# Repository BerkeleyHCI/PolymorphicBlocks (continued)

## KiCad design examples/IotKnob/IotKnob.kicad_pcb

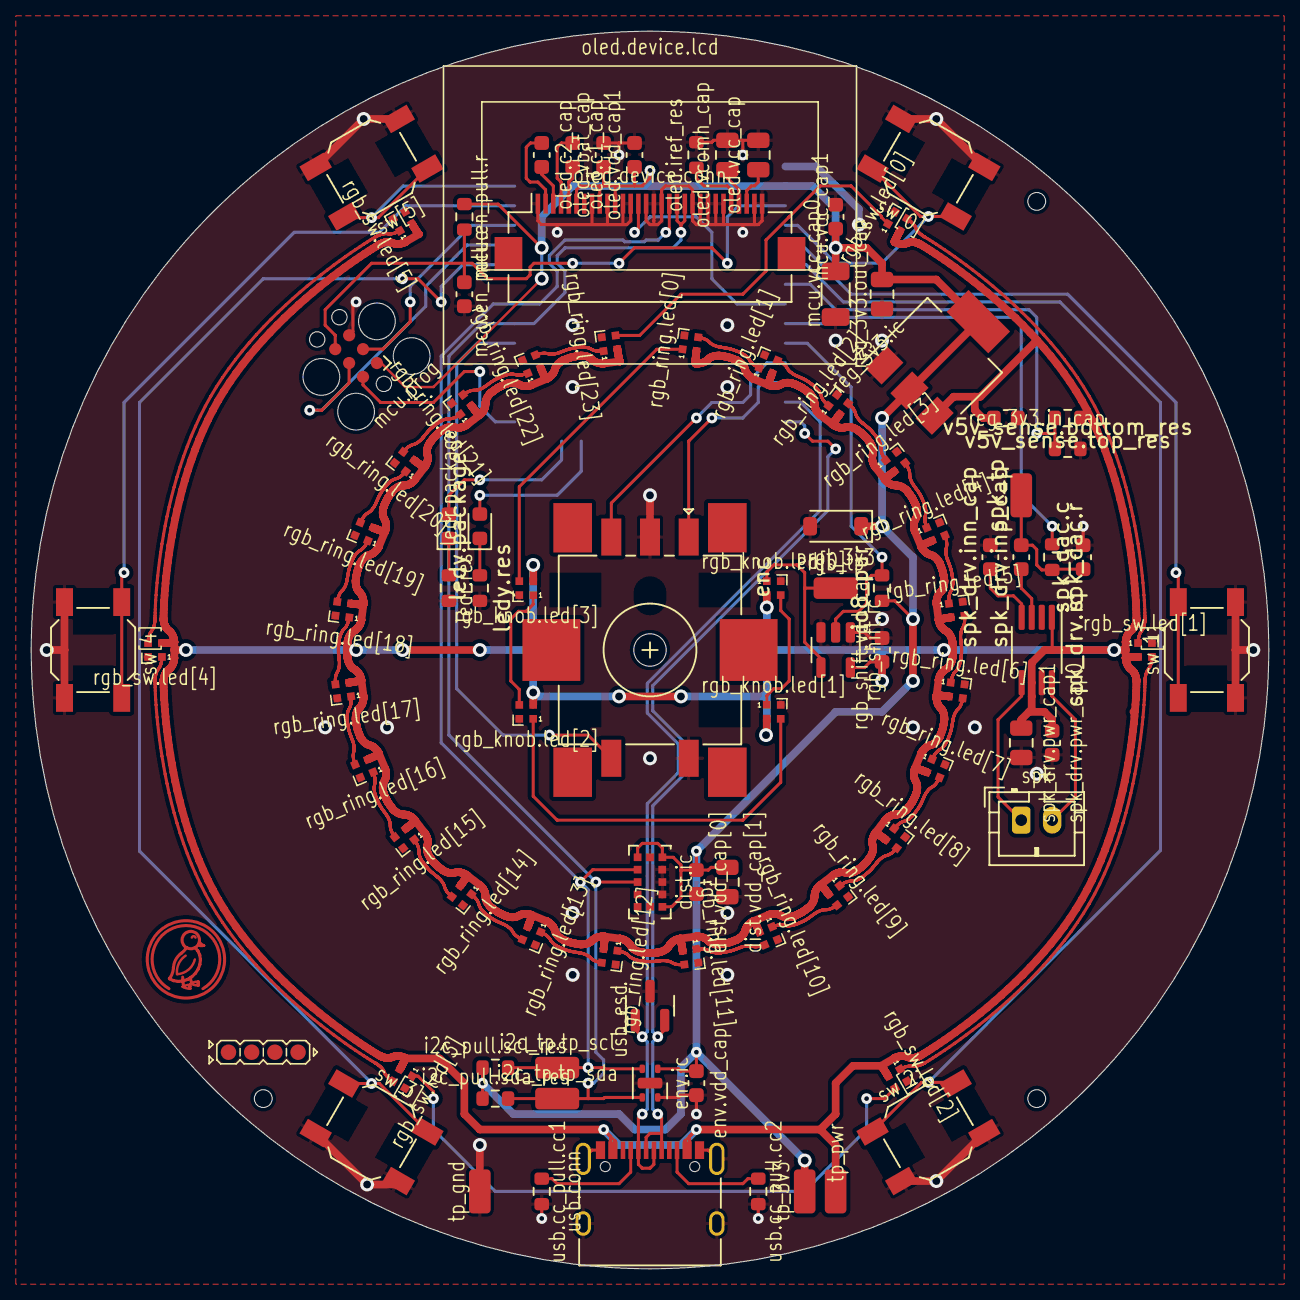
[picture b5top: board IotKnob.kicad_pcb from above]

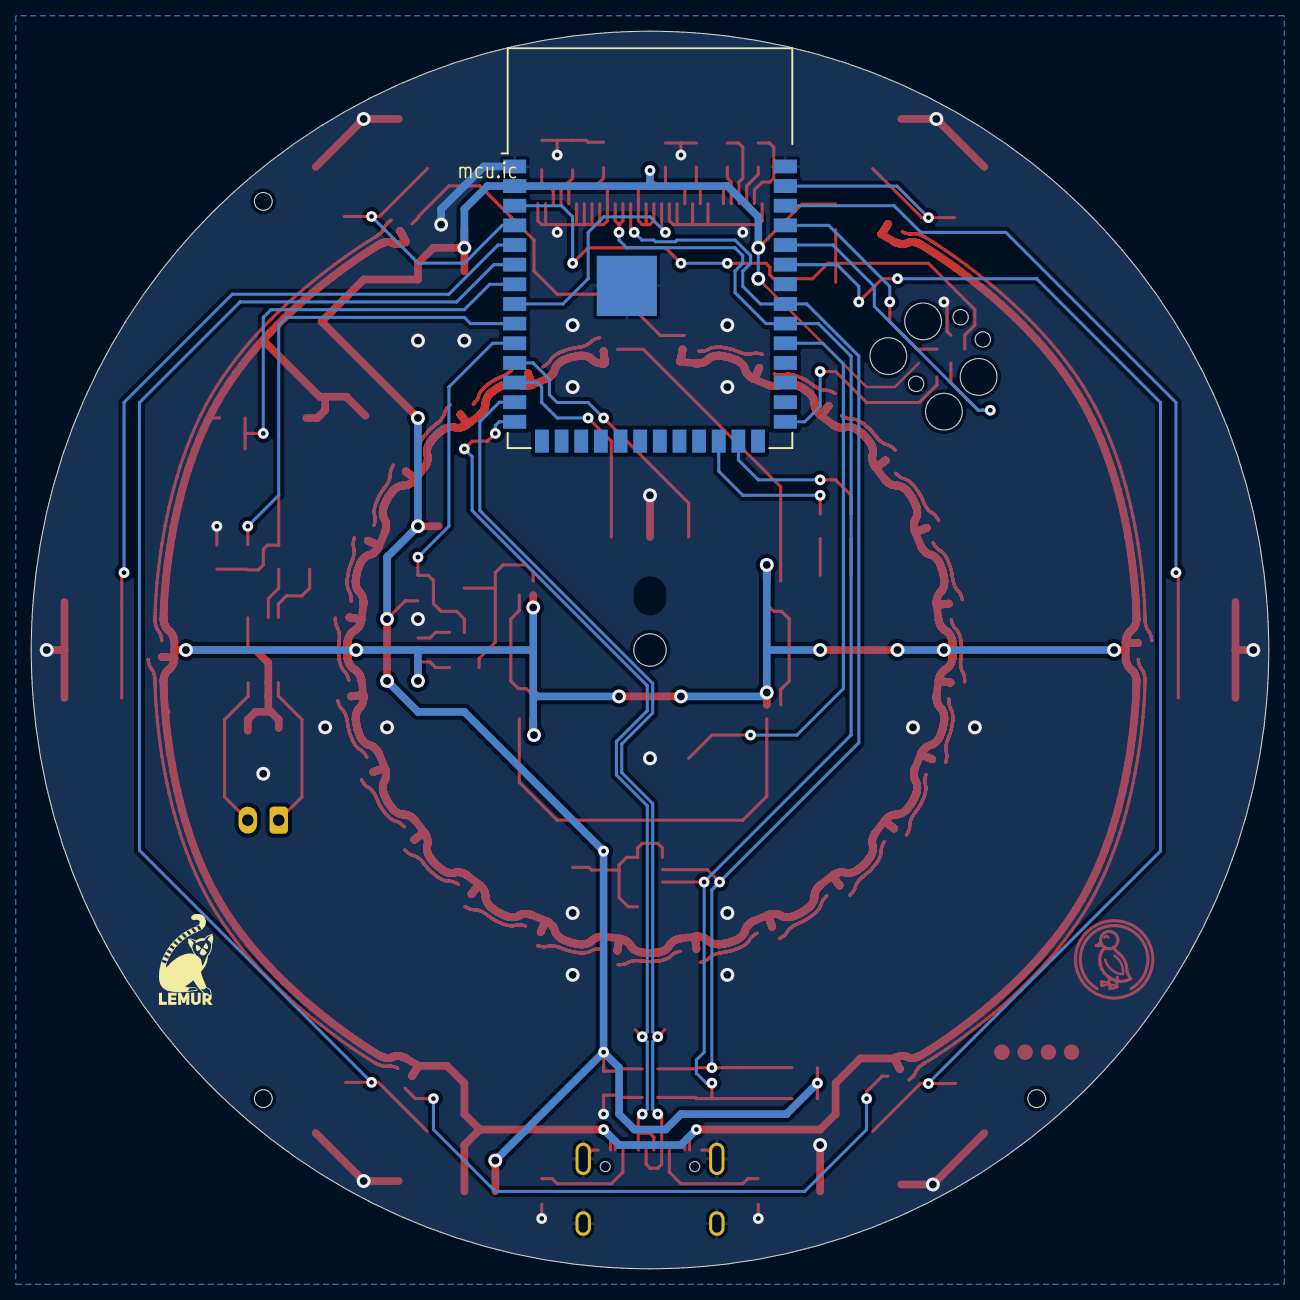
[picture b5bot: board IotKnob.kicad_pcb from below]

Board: 2 copper layers, 80.0 x 80.0 mm, 101 parts (2 on the bottom side), 76 nets.

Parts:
UU4: Duck; Symbol_Duckling
UU5: Lemur; Symbol_LemurSmall
UU6: IdDots4; Indicator_IdDots_4
dist.ic: VL53L0X (STMicroelectronics); ST_VL53L0X
dist.vdd_cap[0]: C_0603_1608Metric
dist.vdd_cap[1]: C_0805_2012Metric
enc: EC11J1525402 (Alps Alpine); RotaryEncoder_Alps_EC11J15-Switch
env.ic: SHTC3 (Sensirion AG); Sensirion_DFN-4-1EP_2x2mm_P1mm_EP0.7x1.6mm
env.vdd_cap: C_0603_1608Metric
i2c_pull.scl_res, i2c_pull.sda_res: R_0603_1608Metric
i2c_tp.tp_scl: 5015 (Keystone) - i2c_chain_0.scl; TestPoint_TE_RCT_0805
i2c_tp.tp_sda: 5015 (Keystone) - i2c_tp._io_sda_link; TestPoint_TE_RCT_0805
io8_pur: R_0603_1608Metric
jlc_th.th1, jlc_th.th2, jlc_th.th3: JlcToolingHole_1.152mm
ledr.package: KT-0603R (Hubei KENTO Elec) - Red 615~630nm 1.9~2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; LED_0603_1608Metric
ledr.res: R_0603_1608Metric
ledy.package: LED_0603_1608Metric
ledy.res: R_0603_1608Metric
mcu.en_pull.c, mcu.vcc_cap1: C_0603_1608Metric
mcu.en_pull.r: R_0603_1608Metric
mcu.ic: ESP32-S3-WROOM-1-N16R8 (Espressif Systems); ESP32-S3-WROOM-1
mcu.prog: Tag-Connect_TC2030-IDC-FP_2x03_P1.27mm_Vertical
mcu.vcc_cap0: C_1206_3216Metric
oled.c1_cap, oled.c2_cap, oled.vbat_cap, oled.vdd_cap1: C_0603_1608Metric
oled.device.conn: AFC01-S30FCA-00 (Jushuo); Hirose_FH12-30S-0.5SH_1x30-1MP_P0.50mm_Horizontal
oled.device.lcd: ER-OLED-0.96-1.1 (EastRising); Lcd_Er_Oled0.96_1.1_Outline
oled.iref_res: R_0603_1608Metric
oled.vcc_cap, oled.vcomh_cap: C_0805_2012Metric
prot_3v3: BZT52C3V6 (SMC(Sangdest Microelectronicstronic (N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; D_SOD-123
reg_3v3.ic: LDL1117S33R (STMicroelectronics); SOT-223-3_TabPin2
reg_3v3.in_cap: C_0603_1608Metric
reg_3v3.out_cap: C_0805_2012Metric
rgb_knob.led[0], rgb_knob.led[1], rgb_knob.led[2], rgb_knob.led[3]: SK6805-EC15 (Opsco Optoelectronics); LED_SK6812_EC15_1.5x1.5mm
rgb_ring.led[0], rgb_ring.led[1], rgb_ring.led[2], rgb_ring.led[3], rgb_ring.led[4], rgb_ring.led[5], rgb_ring.led[6], rgb_ring.led[7], rgb_ring.led[8], rgb_ring.led[9], rgb_ring.led[10], rgb_ring.led[11], rgb_ring.led[12], rgb_ring.led[13], rgb_ring.led[14], rgb_ring.led[15], rgb_ring.led[16], rgb_ring.led[17], rgb_ring.led[18], rgb_ring.led[19], rgb_ring.led[20], rgb_ring.led[21], rgb_ring.led[22], rgb_ring.led[23]: SK6805-EC15 (Opsco Optoelectronics); LED_SK6812_EC15_1.5x1.5mm
rgb_shift.ic: 74AHCT1G125W5-7 (Diodes Incorporated); SOT-23-5
rgb_shift.vdd_cap: C_0603_1608Metric
rgb_sw.led[0], rgb_sw.led[1], rgb_sw.led[2], rgb_sw.led[3], rgb_sw.led[4], rgb_sw.led[5]: SK6805-EC15 (Opsco Optoelectronics); LED_SK6812_EC15_1.5x1.5mm
rgb_tp: 5015 (Keystone) - _rgb_shift_output_link; TestPoint_TE_RCT_0805
spk: B2B-PH-K (JST); JST_PH_B2B-PH-K_1x02_P2.00mm_Vertical
spk_dac.c: C_0603_1608Metric
spk_dac.r: R_0603_1608Metric
spk_drv.ic: PAM8302AASCR (Diodes Incorporated); MSOP-8_3x3mm_P0.65mm
spk_drv.inn_cap, spk_drv.inp_cap, spk_drv.pwr_cap0: C_0603_1608Metric
spk_drv.pwr_cap1: C_0805_2012Metric
spk_tp: 5015 (Keystone) - _spk_dac_output_link; TestPoint_TE_RCT_0805
sw[0], sw[1], sw[2], sw[3], sw[4], sw[5]: 5.1mm switch; SW_SPST_SKQG_WithoutStem
tp_3v3: 5015 (Keystone) - v3v3; TestPoint_TE_RCT_0805
tp_gnd: 5015 (Keystone) - gnd; TestPoint_TE_RCT_0805
tp_pwr: 5015 (Keystone) - vusb; TestPoint_TE_RCT_0805
usb.cc_pull.cc1, usb.cc_pull.cc2: R_0603_1608Metric
usb.conn: COM-15111 (Sparkfun); USB_C_Receptacle_XKB_U262-16XN-4BVC11
usb_esd: PESD5V0X1BT (Nexperia); SOT-23
v5v_sense.bottom_res, v5v_sense.top_res: R_0603_1608Metric

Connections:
enc.a: enc.A, mcu.ic.12
enc.b: enc.B, mcu.ic.11
enc.sw: enc.S1, mcu.ic.31
gnd: dist.ic.2, dist.ic.3, dist.ic.4, dist.ic.6, dist.ic.12, dist.vdd_cap[0].2, dist.vdd_cap[1].2, enc.C, enc.S2, env.ic.4, env.ic.5, env.vdd_cap.2, ledr.res.2, ledy.res.2, mcu.en_pull.c.2, mcu.ic.1, mcu.ic.40, mcu.ic.41, mcu.prog.5, mcu.vcc_cap0.2, mcu.vcc_cap1.2, oled.device.conn.1, oled.device.conn.8, oled.device.conn.10, oled.device.conn.12, oled.device.conn.13, oled.device.conn.15, oled.device.conn.16, oled.device.conn.17, oled.device.conn.21, oled.device.conn.22, oled.device.conn.23, oled.device.conn.24, oled.device.conn.25, oled.device.conn.29, oled.device.conn.30, oled.iref_res.2, oled.vbat_cap.2, oled.vcc_cap.2, oled.vcomh_cap.2, oled.vdd_cap1.2, prot_3v3.2, reg_3v3.ic.1, reg_3v3.in_cap.2, reg_3v3.out_cap.2, rgb_knob.led[0].4, rgb_knob.led[1].4, rgb_knob.led[2].4, rgb_knob.led[3].4, rgb_ring.led[0].4, rgb_ring.led[1].4, rgb_ring.led[2].4, rgb_ring.led[3].4, rgb_ring.led[4].4, rgb_ring.led[5].4, rgb_ring.led[6].4, rgb_ring.led[7].4, rgb_ring.led[8].4, rgb_ring.led[9].4, rgb_ring.led[10].4, rgb_ring.led[11].4, rgb_ring.led[12].4, rgb_ring.led[13].4, rgb_ring.led[14].4, rgb_ring.led[15].4, rgb_ring.led[16].4, rgb_ring.led[17].4, rgb_ring.led[18].4, rgb_ring.led[19].4, rgb_ring.led[20].4, rgb_ring.led[21].4, rgb_ring.led[22].4, rgb_ring.led[23].4, rgb_shift.ic.1, rgb_shift.ic.3, rgb_shift.vdd_cap.2, rgb_sw.led[0].4, rgb_sw.led[1].4, rgb_sw.led[2].4, rgb_sw.led[3].4, rgb_sw.led[4].4, rgb_sw.led[5].4, spk_dac.c.2, spk_drv.ic.7, spk_drv.inn_cap.2, spk_drv.pwr_cap0.2, spk_drv.pwr_cap1.2, sw[0].2, sw[1].2, sw[2].2, sw[3].2, sw[4].2, sw[5].2, tp_gnd.1, usb.cc_pull.cc1.1, usb.cc_pull.cc2.1, usb.conn.A1, usb.conn.A12, usb.conn.B1, usb.conn.B12, usb.conn.S1, usb_esd.3, v5v_sense.bottom_res.2
i2c_chain_0.scl: dist.ic.10, env.ic.2, i2c_pull.scl_res.2, i2c_tp.tp_scl.1, mcu.ic.33, oled.device.conn.18
i2c_chain_0.sda: dist.ic.9, env.ic.3, i2c_pull.sda_res.2, i2c_tp.tp_sda.1, mcu.ic.32, oled.device.conn.19, oled.device.conn.20
io8_pur.io: io8_pur.2, mcu.ic.10, rgb_shift.ic.2
ledr.res.a: ledr.package.1, ledr.res.1
ledr.signal: ledr.package.2, mcu.ic.25
ledy.res.a: ledy.package.1, ledy.res.1
ledy.signal: ledy.package.2, mcu.ic.24
mcu.program_boot_node: mcu.ic.27, mcu.prog.2
mcu.program_en_node: mcu.en_pull.c.1, mcu.en_pull.r.2, mcu.ic.3, mcu.prog.6
mcu.program_uart_node.a_tx: mcu.ic.37, mcu.prog.3
mcu.program_uart_node.b_tx: mcu.ic.36, mcu.prog.4
oled.c1_cap.neg: oled.c1_cap.2, oled.device.conn.5
oled.c1_cap.pos: oled.c1_cap.1, oled.device.conn.4
oled.c2_cap.neg: oled.c2_cap.2, oled.device.conn.3
oled.c2_cap.pos: oled.c2_cap.1, oled.device.conn.2
oled.device.vcc: oled.device.conn.28, oled.vcc_cap.1
oled.device.vcomh: oled.device.conn.27, oled.vcomh_cap.1
oled.iref_res.a: oled.device.conn.26, oled.iref_res.1
oled.reset: mcu.ic.8, oled.device.conn.14
rgb_knob.dout: rgb_knob.led[3].3, rgb_ring.led[0].1
rgb_knob.led[0].dout: rgb_knob.led[0].3, rgb_knob.led[1].1
rgb_knob.led[1].dout: rgb_knob.led[1].3, rgb_knob.led[2].1
rgb_knob.led[2].dout: rgb_knob.led[2].3, rgb_knob.led[3].1
rgb_ring.dout: rgb_ring.led[23].3, rgb_sw.led[0].1
rgb_ring.led[0].dout: rgb_ring.led[0].3, rgb_ring.led[1].1
rgb_ring.led[1].dout: rgb_ring.led[1].3, rgb_ring.led[2].1
rgb_ring.led[2].dout: rgb_ring.led[2].3, rgb_ring.led[3].1
rgb_ring.led[3].dout: rgb_ring.led[3].3, rgb_ring.led[4].1
rgb_ring.led[4].dout: rgb_ring.led[4].3, rgb_ring.led[5].1
rgb_ring.led[5].dout: rgb_ring.led[5].3, rgb_ring.led[6].1
rgb_ring.led[6].dout: rgb_ring.led[6].3, rgb_ring.led[7].1
rgb_ring.led[7].dout: rgb_ring.led[7].3, rgb_ring.led[8].1
rgb_ring.led[8].dout: rgb_ring.led[8].3, rgb_ring.led[9].1
rgb_ring.led[9].dout: rgb_ring.led[9].3, rgb_ring.led[10].1
rgb_ring.led[10].dout: rgb_ring.led[10].3, rgb_ring.led[11].1
rgb_ring.led[11].dout: rgb_ring.led[11].3, rgb_ring.led[12].1
rgb_ring.led[12].dout: rgb_ring.led[12].3, rgb_ring.led[13].1
rgb_ring.led[13].dout: rgb_ring.led[13].3, rgb_ring.led[14].1
rgb_ring.led[14].dout: rgb_ring.led[14].3, rgb_ring.led[15].1
rgb_ring.led[15].dout: rgb_ring.led[15].3, rgb_ring.led[16].1
rgb_ring.led[16].dout: rgb_ring.led[16].3, rgb_ring.led[17].1
rgb_ring.led[17].dout: rgb_ring.led[17].3, rgb_ring.led[18].1
rgb_ring.led[18].dout: rgb_ring.led[18].3, rgb_ring.led[19].1
rgb_ring.led[19].dout: rgb_ring.led[19].3, rgb_ring.led[20].1
rgb_ring.led[20].dout: rgb_ring.led[20].3, rgb_ring.led[21].1
rgb_ring.led[21].dout: rgb_ring.led[21].3, rgb_ring.led[22].1
rgb_ring.led[22].dout: rgb_ring.led[22].3, rgb_ring.led[23].1
rgb_shift.output: rgb_knob.led[0].1, rgb_shift.ic.4, rgb_tp.1
rgb_sw.led[0].dout: rgb_sw.led[0].3, rgb_sw.led[1].1
rgb_sw.led[1].dout: rgb_sw.led[1].3, rgb_sw.led[2].1
rgb_sw.led[2].dout: rgb_sw.led[2].3, rgb_sw.led[3].1
rgb_sw.led[3].dout: rgb_sw.led[3].3, rgb_sw.led[4].1
rgb_sw.led[4].dout: rgb_sw.led[4].3, rgb_sw.led[5].1
spk_dac.input: mcu.ic.9, spk_dac.r.1
spk_dac.output: spk_dac.c.1, spk_dac.r.2, spk_drv.inp_cap.2, spk_tp.1
spk_drv.inn_cap.pos: spk_drv.ic.4, spk_drv.inn_cap.1
spk_drv.inp_cap.pos: spk_drv.ic.3, spk_drv.inp_cap.1
spk_drv.spk.a: spk.1, spk_drv.ic.5
spk_drv.spk.b: spk.2, spk_drv.ic.8
sw[0].out: mcu.ic.4, sw[0].1
sw[1].out: mcu.ic.5, sw[1].1
sw[2].out: mcu.ic.6, sw[2].1
sw[3].out: mcu.ic.35, sw[3].1
sw[4].out: mcu.ic.38, sw[4].1
sw[5].out: mcu.ic.39, sw[5].1
usb.conn.A5: usb.cc_pull.cc1.2, usb.conn.A5
usb.conn.B5: usb.cc_pull.cc2.2, usb.conn.B5
usb_chain_0.d_N: mcu.ic.13, usb.conn.A7, usb.conn.B7, usb_esd.1
usb_chain_0.d_P: mcu.ic.14, usb.conn.A6, usb.conn.B6, usb_esd.2
v3v3: dist.ic.1, dist.ic.5, dist.ic.11, dist.vdd_cap[0].1, dist.vdd_cap[1].1, env.ic.1, env.vdd_cap.1, i2c_pull.scl_res.1, i2c_pull.sda_res.1, io8_pur.1, mcu.en_pull.r.1, mcu.ic.2, mcu.prog.1, mcu.vcc_cap0.1, mcu.vcc_cap1.1, oled.device.conn.6, oled.device.conn.9, oled.device.conn.11, oled.vbat_cap.1, oled.vdd_cap1.1, prot_3v3.1, reg_3v3.ic.2, reg_3v3.out_cap.1, tp_3v3.1
v5v_sense.output: mcu.ic.7, v5v_sense.bottom_res.1, v5v_sense.top_res.2
vusb: reg_3v3.ic.3, reg_3v3.in_cap.1, rgb_knob.led[0].2, rgb_knob.led[1].2, rgb_knob.led[2].2, rgb_knob.led[3].2, rgb_ring.led[0].2, rgb_ring.led[1].2, rgb_ring.led[2].2, rgb_ring.led[3].2, rgb_ring.led[4].2, rgb_ring.led[5].2, rgb_ring.led[6].2, rgb_ring.led[7].2, rgb_ring.led[8].2, rgb_ring.led[9].2, rgb_ring.led[10].2, rgb_ring.led[11].2, rgb_ring.led[12].2, rgb_ring.led[13].2, rgb_ring.led[14].2, rgb_ring.led[15].2, rgb_ring.led[16].2, rgb_ring.led[17].2, rgb_ring.led[18].2, rgb_ring.led[19].2, rgb_ring.led[20].2, rgb_ring.led[21].2, rgb_ring.led[22].2, rgb_ring.led[23].2, rgb_shift.ic.5, rgb_shift.vdd_cap.1, rgb_sw.led[0].2, rgb_sw.led[1].2, rgb_sw.led[2].2, rgb_sw.led[3].2, rgb_sw.led[4].2, rgb_sw.led[5].2, spk_drv.ic.1, spk_drv.ic.6, spk_drv.pwr_cap0.1, spk_drv.pwr_cap1.1, tp_pwr.1, usb.conn.A4, usb.conn.A9, usb.conn.B4, usb.conn.B9, v5v_sense.top_res.1

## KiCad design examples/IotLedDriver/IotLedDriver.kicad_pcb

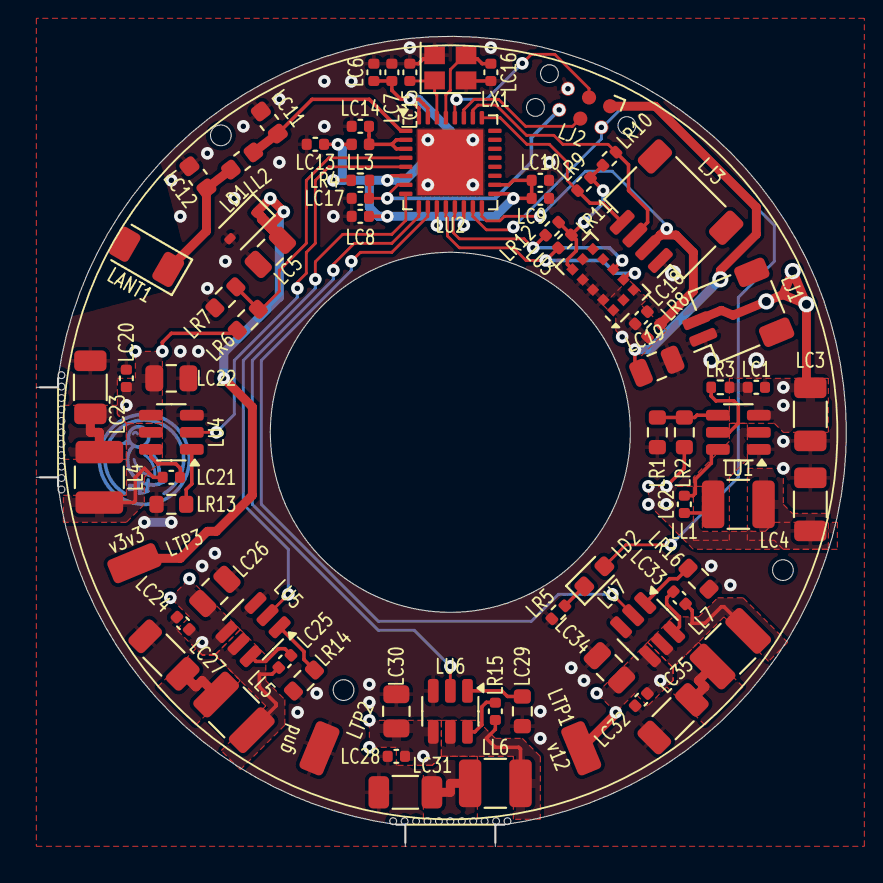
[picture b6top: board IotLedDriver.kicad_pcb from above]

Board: 2 copper layers, 45.0 x 45.0 mm, 79 parts (1 on the bottom side), 43 nets.

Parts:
LANT1: mcu.ant; D_1206_3216Metric
LC1: reg_3v3.hf_in_cap; C_0402_1005Metric
LC2: reg_3v3.boot_cap; C_0402_1005Metric
LC3: reg_3v3.power_path.in_cap; C_1206_3216Metric
LC4: reg_3v3.power_path.out_cap; C_1206_3216Metric
LC5: mcu.vdd_bulk_cap; C_0805_2012Metric
LC6: mcu.vdda_cap0; C_0402_1005Metric
LC7: mcu.vdda_cap1; C_0402_1005Metric
LC8: mcu.vddrtc_cap; C_0402_1005Metric
LC9: mcu.vddcpu_cap; C_0402_1005Metric
LC10: mcu.vddspi_cap; C_0402_1005Metric
LC11: mcu.pi.c1; C_0603_1608Metric
LC12: mcu.pi.c2; C_0603_1608Metric
LC13: mcu.vdd3p3_l_cap; C_0402_1005Metric
LC14: mcu.vdd3p3_cap; C_0402_1005Metric
LC15: mcu.crystal.cap_a; C_0402_1005Metric
LC16: mcu.crystal.cap_b; C_0402_1005Metric
LC17: mcu.en_pull.c; C_0402_1005Metric
LC18: tof.vdd_cap[0]; C_0402_1005Metric
LC19: tof.vdd_cap[1]; C_0805_2012Metric
LC20: led_drv[0].cap; C_0402_1005Metric
LC21: led_drv[0].boot_cap; C_0402_1005Metric
LC22: led_drv[0].power_path.in_cap; C_0805_2012Metric
LC23: led_drv[0].power_path.out_cap; C_1206_3216Metric
LC24: led_drv[1].cap; C_0402_1005Metric
LC25: led_drv[1].boot_cap; C_0402_1005Metric
LC26: led_drv[1].power_path.in_cap; C_0805_2012Metric
LC27: led_drv[1].power_path.out_cap; C_1206_3216Metric
LC28: led_drv[2].cap; C_0402_1005Metric
LC29: led_drv[2].boot_cap; C_0402_1005Metric
LC30: led_drv[2].power_path.in_cap; C_0805_2012Metric
LC31: led_drv[2].power_path.out_cap; C_1206_3216Metric
LC32: led_drv[3].cap; C_0402_1005Metric
LC33: led_drv[3].boot_cap; C_0402_1005Metric
LC34: led_drv[3].power_path.in_cap; C_0805_2012Metric
LC35: led_drv[3].power_path.out_cap; C_1206_3216Metric
LD1: prot_3v3; D_SOD-323
LD2: ledr.package; LED_0603_1608Metric
LH1: jlc_th.th1; JlcToolingHole_1.152mm
LH2: jlc_th.th2; JlcToolingHole_1.152mm
LH3: jlc_th.th3; JlcToolingHole_1.152mm
LJ1: pwr; JST_SH_SM02B-SRSS-TB_1x02-1MP_P1.00mm_Horizontal
LJ2: mcu.prog; Tag-Connect_TC2030-IDC-NL_2x03_P1.27mm_Vertical
LJ3: qwiic; JST_SH_SM04B-SRSS-TB_1x04-1MP_P1.00mm_Horizontal
LL1: reg_3v3.power_path.inductor; L_1210_3225Metric
LL2: mcu.pi.l; L_0603_1608Metric
LL3: mcu.vdd3p3_l; L_0402_1005Metric
LL4: led_drv[0].power_path.inductor; L_1210_3225Metric
LL5: led_drv[1].power_path.inductor; L_1210_3225Metric
LL6: led_drv[2].power_path.inductor; L_1210_3225Metric
LL7: led_drv[3].power_path.inductor; L_1210_3225Metric
LR1: reg_3v3.fb.top_res; R_0603_1608Metric
LR2: reg_3v3.fb.bottom_res; R_0603_1608Metric
LR3: reg_3v3.en_res; R_0402_1005Metric
LR4: mcu.en_pull.r; R_0402_1005Metric
LR5: ledr.res; R_0402_1005Metric
LR6: v12_sense.top_res; R_0603_1608Metric
LR7: v12_sense.bottom_res; R_0603_1608Metric
LR8: qwiic_pwr_res; R_0402_1005Metric
LR9: qwiic_pull.scl_res; R_0402_1005Metric
LR10: qwiic_pull.sda_res; R_0402_1005Metric
LR11: tof_pull.scl_res; R_0402_1005Metric
LR12: tof_pull.sda_res; R_0402_1005Metric
LR13: led_drv[0].rsense; R_0603_1608Metric
LR14: led_drv[1].rsense; R_0603_1608Metric
LR15: led_drv[2].rsense; R_0603_1608Metric
LR16: led_drv[3].rsense; R_0603_1608Metric
LTP1: v12; TestPoint_TE_RCT_0805
LTP2: gnd; TestPoint_TE_RCT_0805
LTP3: v3v3; TestPoint_TE_RCT_0805
LU1: reg_3v3.ic; SOT-23-6
LU2: mcu.ic; QFN-32-1EP_5x5mm_P0.5mm_EP3.65x3.65mm
LU3: tof.ic; ST_VL53L0X
LU4: led_drv[0].ic; SOT-23-6
LU5: led_drv[1].ic; SOT-23-6
LU6: led_drv[2].ic; SOT-23-6
LU7: led_drv[3].ic; SOT-23-6
LX1: mcu.crystal.package; Crystal_SMD_2520-4Pin_2.5x2.0mm
UU4: Duck; Symbol_Duckling

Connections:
Lgnd: LC1.2, LC3.2, LC4.2, LC5.2, LC6.2, LC7.2, LC8.2, LC9.2, LC10.2, LC11.2, LC12.2, LC13.2, LC14.2, LC15.2, LC16.2, LC17.2, LC18.2, LC19.2, LC20.2, LC22.2, LC23.2, LC24.2, LC26.2, LC27.2, LC28.2, LC30.2, LC31.2, LC32.2, LC34.2, LC35.2, LD1.2, LJ1.1, LJ2.5, LJ3.1, LR2.2, LR5.2, LR7.2, LR13.1, LR14.1, LR15.1, LR16.1, LTP2.1, LU1.1, LU2.33, LU3.2, LU3.3, LU3.4, LU3.6, LU3.12, LU4.3, LU5.3, LU6.3, LU7.3, LX1.2, LX1.4
Lled_drv[0].boot_cap.neg: LC21.2, LL4.1, LU4.5
Lled_drv[0].boot_cap.pos: LC21.1, LU4.6
Lled_drv[0].leda: LC23.1, LL4.2
Lled_drv[0].ledk: LR13.2, LU4.1
Lled_drv[0].pwm: LU2.5, LU4.2
Lled_drv[1].boot_cap.neg: LC25.2, LL5.1, LU5.5
Lled_drv[1].boot_cap.pos: LC25.1, LU5.6
Lled_drv[1].leda: LC27.1, LL5.2
Lled_drv[1].ledk: LR14.2, LU5.1
Lled_drv[1].pwm: LU2.8, LU5.2
Lled_drv[2].boot_cap.neg: LC29.2, LL6.1, LU6.5
Lled_drv[2].boot_cap.pos: LC29.1, LU6.6
Lled_drv[2].leda: LC31.1, LL6.2
Lled_drv[2].ledk: LR15.2, LU6.1
Lled_drv[2].pwm: LU2.9, LU6.2
Lled_drv[3].boot_cap.neg: LC33.2, LL7.1, LU7.5
Lled_drv[3].boot_cap.pos: LC33.1, LU7.6
Lled_drv[3].leda: LC35.1, LL7.2
Lled_drv[3].ledk: LR16.2, LU7.1
Lled_drv[3].pwm: LU2.10, LU7.2
Lledr.res.a: LD2.1, LR5.1
Lmcu.ic.lna_in: LC11.1, LL2.1, LU2.1
Lmcu.ic.vdd3p3: LC14.1, LL3.2, LU2.2, LU2.3
Lmcu.pi.output: LANT1.1, LC12.1, LL2.2
Lmcu.program_boot_node: LD2.2, LJ2.2, LU2.15
Lmcu.program_en_node: LC17.1, LJ2.6, LR4.2, LU2.7
Lmcu.program_uart_node.a_tx: LJ2.3, LU2.28
Lmcu.program_uart_node.b_tx: LJ2.4, LU2.27
Lmcu.xtal_node.xi: LC15.1, LU2.30, LX1.1
Lmcu.xtal_node.xo: LC16.1, LU2.29, LX1.3
Lqwiic_i2c.scl: LJ3.4, LR9.2, LU2.25
Lqwiic_i2c.sda: LJ3.3, LR10.2, LU2.26
Lqwiic_pwr_res.pwr_out: LJ3.2, LR8.2, LU2.16
Lreg_3v3.boot_cap.neg: LC2.2, LL1.1, LU1.2
Lreg_3v3.boot_cap.pos: LC2.1, LU1.6
Lreg_3v3.en_res.b: LR3.2, LU1.5
Lreg_3v3.fb.output: LR1.2, LR2.1, LU1.4
Ltof_pull.i2c.scl: LR11.2, LU2.12, LU3.10
Ltof_pull.i2c.sda: LR12.2, LU2.13, LU3.9
Lv3v3: LC4.1, LC5.1, LC6.1, LC7.1, LC8.1, LC9.1, LC10.1, LC13.1, LC18.1, LC19.1, LD1.1, LJ2.1, LL1.2, LL3.1, LR1.1, LR4.1, LR8.1, LR9.1, LR10.1, LR11.1, LR12.1, LTP3.1, LU2.6, LU2.11, LU2.14, LU2.17, LU2.18, LU2.31, LU2.32, LU3.1, LU3.5, LU3.11
Lv12: LC1.1, LC3.1, LC20.1, LC22.1, LC24.1, LC26.1, LC28.1, LC30.1, LC32.1, LC34.1, LJ1.2, LR3.1, LR6.1, LTP1.1, LU1.3, LU4.4, LU5.4, LU6.4, LU7.4
Lv12_sense.output: LR6.2, LR7.1, LU2.4

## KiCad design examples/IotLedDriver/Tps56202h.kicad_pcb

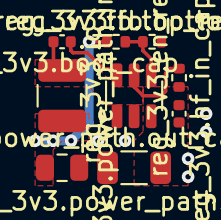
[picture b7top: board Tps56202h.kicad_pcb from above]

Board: 2 copper layers, 9 parts (0 on the bottom side), 7 nets.

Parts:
reg_3v3.boot_cap: 16V 100nF X7R ±10% 0402 Multilayer Ceramic Capaci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; C_0402_1005Metric
reg_3v3.en_res, reg_3v3.fb.bottom_res, reg_3v3.fb.top_res: ±1% 1/16W Thick Film Resistors 50V ±100ppm/? -55?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; R_0402_1005Metric
reg_3v3.hf_in_cap: 50V 100nF X7R ±10% 0402 Multilayer Ceramic Capaci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; C_0402_1005Metric
reg_3v3.ic: TPS54202H; SOT-23-6
reg_3v3.power_path.in_cap: 25V 22uF X5R ±10% 1206 Multilayer Ceramic Capacit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; C_1206_3216Metric
reg_3v3.power_path.inductor: 620mA 22uH ±10% 270m? 1210 Inductors (SMD) ROHS; L_1210_3225Metric
reg_3v3.power_path.out_cap: X5R 25V ±10% 10uF 0805 Multilayer Ceramic Capacit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; C_0805_2012Metric

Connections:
Lgnd: reg_3v3.fb.bottom_res.2, reg_3v3.hf_in_cap.2, reg_3v3.ic.1, reg_3v3.power_path.in_cap.2, reg_3v3.power_path.out_cap.2
Lreg_3v3.boot_cap.neg: reg_3v3.boot_cap.2, reg_3v3.ic.2, reg_3v3.power_path.inductor.1
Lreg_3v3.boot_cap.pos: reg_3v3.boot_cap.1, reg_3v3.ic.6
Lreg_3v3.en_res.b: reg_3v3.en_res.2, reg_3v3.ic.5
Lreg_3v3.fb.output: reg_3v3.fb.bottom_res.1, reg_3v3.fb.top_res.2, reg_3v3.ic.4
Lv3v3: reg_3v3.fb.top_res.1, reg_3v3.power_path.inductor.2, reg_3v3.power_path.out_cap.1
Lv12: reg_3v3.en_res.1, reg_3v3.hf_in_cap.1, reg_3v3.ic.3, reg_3v3.power_path.in_cap.1
